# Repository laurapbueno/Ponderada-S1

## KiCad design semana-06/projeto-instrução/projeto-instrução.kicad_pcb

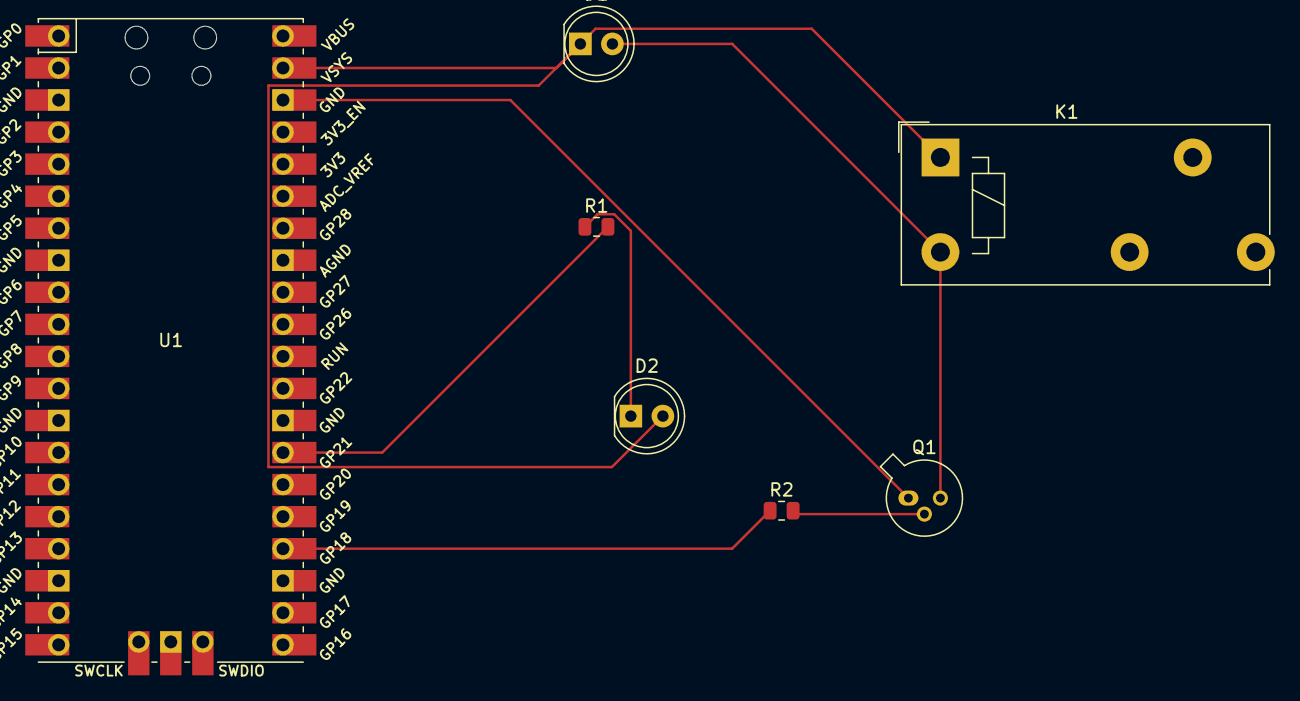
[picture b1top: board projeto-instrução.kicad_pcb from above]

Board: 2 copper layers, 7 parts (0 on the bottom side), 7 nets.

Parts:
D1, D2: LED; LED_D5.0mm_Clear
K1: Relay_SPDT; Relay_SPDT_Finder_40.51
Q1: BC107; TO-18-3
R1, R2: R; R_0805_2012Metric
U1: Pico; RPi_Pico_SMD_TH

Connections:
GND: Q1.1 (E), U1.38 (GND)
unnamed: D1.2 (A), K1.A2, Q1.3 (C)
unnamed: D2.1 (K), R1.1
unnamed: Q1.2 (B), R2.2
VCC: D1.1 (K), D2.2 (A), K1.A1, U1.39 (VSYS)
saida_led: R1.2, U1.27 (GPIO21)
sinal: R2.1, U1.24 (GPIO18)

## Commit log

2024-02-08 projeto docu
2024-02-15 Docusaurus
2024-02-15 teste
2024-02-19 update ponderada
2024-03-01 Ponderada Semana 3/4
2024-04-01 Ponderada Kicad
2024-04-05 Ponderada FLASK | Semana 07
